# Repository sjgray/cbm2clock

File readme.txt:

CBM-II Clock Board
==================

This is a simple 50/60 Hz clock generator for use on CBM-II machines with replacement
non-original power supplies.

Website
-------

Project information can be found here: cbmsteve.ca/cbm2clock

History
-------
2024-05-11  V1.0 Created.
2024-08-09  V1.0 schematics updated with additional text and parts list (50Hz only so far)
2024-08-09  Website and GitHub created.

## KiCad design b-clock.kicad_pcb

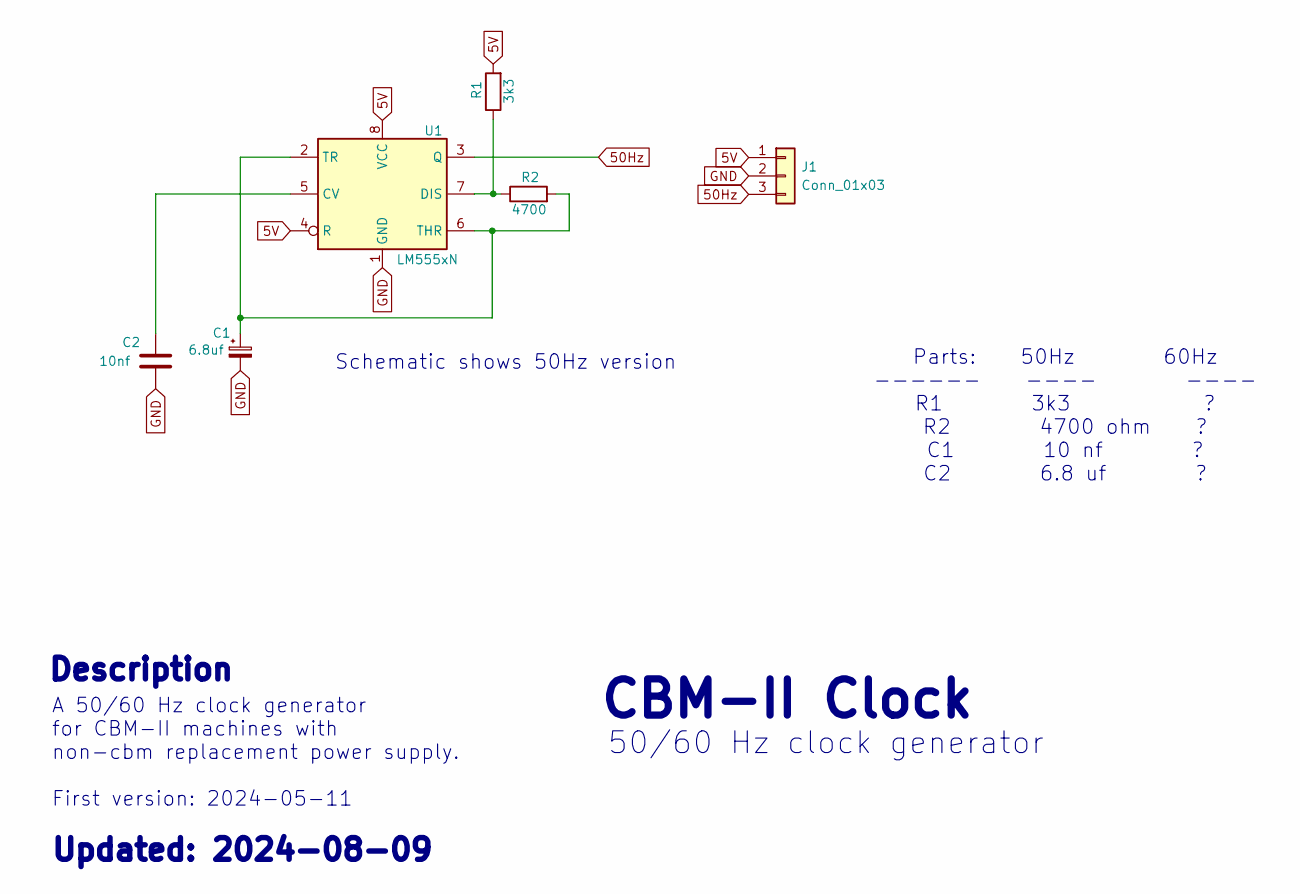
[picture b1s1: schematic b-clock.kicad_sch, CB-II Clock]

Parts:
C1: 6.8uf; CP_Radial_D5.0mm_P2.00mm
C2: 10nf; C_Disc_D3.8mm_W2.6mm_P2.50mm
J1: Conn_01x03; PinHeader_1x03_P2.54mm_Vertical
R1: 3k3; R_Axial_DIN0204_L3.6mm_D1.6mm_P7.62mm_Horizontal
R2: 4700; R_Axial_DIN0204_L3.6mm_D1.6mm_P7.62mm_Horizontal
U1: LM555xN; DIP-8_W7.62mm

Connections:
5V: J1.1, R1.2, U1.4 (R), U1.8 (VCC)
50Hz: J1.3, U1.3 (Q)
GND: C1.2, C2.2, J1.2, U1.1 (GND)
unnamed: C2.1, U1.5 (CV)
unnamed: R1.1, R2.1, U1.7 (DIS)
unnamed: C1.1, R2.2, U1.2 (TR), U1.6 (THR)

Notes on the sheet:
Schematic shows 50Hz version
Parts: 50Hz 60Hz ------ ---- ---- R1 3k3 ? R2 4700 ohm ? C1 10 nf ? C2 6.8 uf ?
Updated: 2024-08-09
CBM-II Clock
Description
50/60 Hz clock generator
A 50/60 Hz clock generator for CBM-II machines with non-cbm replacement power supply. First version: 2024-05-11

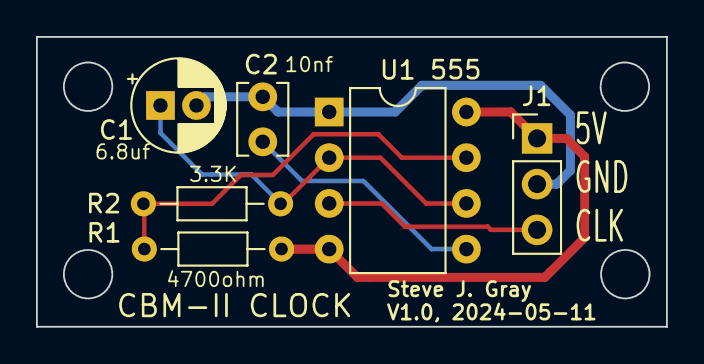
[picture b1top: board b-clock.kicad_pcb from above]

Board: 2 copper layers, 35.0 x 16.1 mm, 6 parts (0 on the bottom side), 6 nets.

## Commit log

2024-08-09 V1.0 Initial design
    V1.0 Kicad design files, gerbers, and pictures
